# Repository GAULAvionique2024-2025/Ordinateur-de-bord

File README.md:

<h1 align="center">Ordinateur de bord GAUL 2024-2026</h1>

<p align="left">

</p>

## 🌟 **Main Repo pour l'ODB du GAUL**

Ce projet met en œuvre un MCU associé à divers capteurs et modules pour créer un ordinateur de bord performant, optimisé pour un lancement de fusée de type L4. Ce système embarqué est conçu pour collecter et analyser des données en temps réel, permettant ainsi une évaluation précise des performances de la fusée.
De plus, l’ODB est responsable du déclenchement des charges pyrotechniques utilisées pour le déploiement des parachutes et la séparation des étages de la fusée, assurant ainsi la réussite et la sécurité des différentes phases du vol.
L’ensemble forme un système de télémétrie complet, capable non seulement de mesurer et enregistrer les données de vol, mais aussi d’agir activement sur les systèmes de la fusée au bon moment.

> Pour des explications détaillées sur le rôle et le fonctionnement de chaque composant, consultez :
> - [Explications ODB1](./Documentation/ODB1/Explications.md)
> - [Explications ODB2](./Documentation/ODB2/Explications.md)
> - [Explications ODB3 (ODBlix)](./Documentation/ODB2/Explications.md)

## ⚙️ Fonctionnalités de l’Ordinateur de bord (ODB)

Ce document présente une vue d’ensemble des fonctionnalités offertes par l’ordinateur de bord du GAUL.  
Il s’agit d’un résumé fonctionnel, indépendant des détails d’implémentation propres à chaque version.

### 📊 Acquisition et gestion des données
- Mesure des paramètres de vol (accélération, orientation, altitude, température, etc.)
- Acquisition des données à haute fréquence durant les phases critiques du vol
- Synchronisation temporelle des mesures
- Gestion simultanée de plusieurs capteurs
- Support de la redondance des sources de données

### 💾 Enregistrement et stockage
- Enregistrement complet des données de vol pour analyse post-lancement
- Stockage sur mémoire embarquée et/ou carte SD
- Structuration et horodatage des journaux de vol

### 📡 Télémétrie et communication
- Transmission des données de vol en temps réel vers la station au sol
- Communication radio longue portée
- Communication locale pour configuration, tests et débogage
- Support de protocoles de communication adaptés à l’avionique expérimentale

### 🚦 Gestion des événements de vol
- Détection automatique des différentes phases de vol (lancement, apogée, descente, atterrissage)
- Déclenchement conditionnel des événements critiques
- Commande des charges pyrotechniques (déploiement des parachutes, séparation des étages)
- Mécanismes de sécurité contre les déclenchements inattendus

### 🧭 Navigation et localisation
- Intégration des données de positionnement GPS
- Suivi de la trajectoire de vol
- Assistance à la récupération post-vol
- Compatibilité avec notre système de repérage externe ([IdéFIX](https://github.com/GAULAvionique/IdeFIX))

### 🔍 Diagnostic et supervision
- Surveillance de l’état du système en temps réel
- Indication des statuts de fonctionnement et des erreurs
- Outils d’aide au débogage pour les phases de test
- Retour d’information sonore et/ou visuel

### 🧪 Tests et validation
- Support des essais au sol
- Modes de test et de simulation
- Validation progressive avant intégration en vol
- Exploitation des données de vol pour amélioration continue

## 📚 **Documentation**

Toutes les informations sur les composants hardware / logiciel et les drivers sont disponibles ici :

### **Ordinateur de bord 1**
- [Composantes](./Documentation/ODB1/Composantes.md)
- [Drivers](./Documentation/ODB1/Drivers.md)

### **Ordinateur de bord 2**

- [Composantes](./Documentation/ODB2/Composantes.md)
- [Drivers](./Documentation/ODB2/Drivers.md)

### **Ordinateur de bord 3**

- [Composantes](./Documentation/ODB3/Composantes.md)
- [Drivers](./Documentation/ODB3/Drivers.md)

> [Prise en main des logiciels](./Documentation/Logiciel.md)

### 💡 **Liens Utiles**
- Pour voir la première itération de l'ordinateur de bord, consultez le projet [ODB1](https://github.com/GAULAvionique2023-2024/ODB1_Firmware).
- L'environnement de développement intégré pour STM32 est [STM32CubeIDE](https://www.st.com/en/development-tools/stm32cubeide.html). Un document est disponible pour permettre une [prise en main](./Documentation/Logiciel.md) initiale pour le projet.
- [deepbluembedded](https://deepbluembedded.com/stm32-arm-programming-tutorials/) offre des tutoriels sur la programmation STM32.

> Ce projet essaye de suivre les règles de [Conventional Commits](https://www.conventionalcommits.org/en/v1.0.0/) afin de garder un historique clair et cohérent.

## 👥 **Auteurs et Contributeurs**

- [@SamLol12](https://github.com/SamLol12)
- [@bestrider14](https://github.com/bestrider14)
- [@mathouqc](https://github.com/mathouqc)
- [@vides119](https://github.com/vides119)
- [Autres Participants](./Documentation/Participants.md)

---

🏠 Retour à la [page d'accueil](https://github.com/GAULAvionique)

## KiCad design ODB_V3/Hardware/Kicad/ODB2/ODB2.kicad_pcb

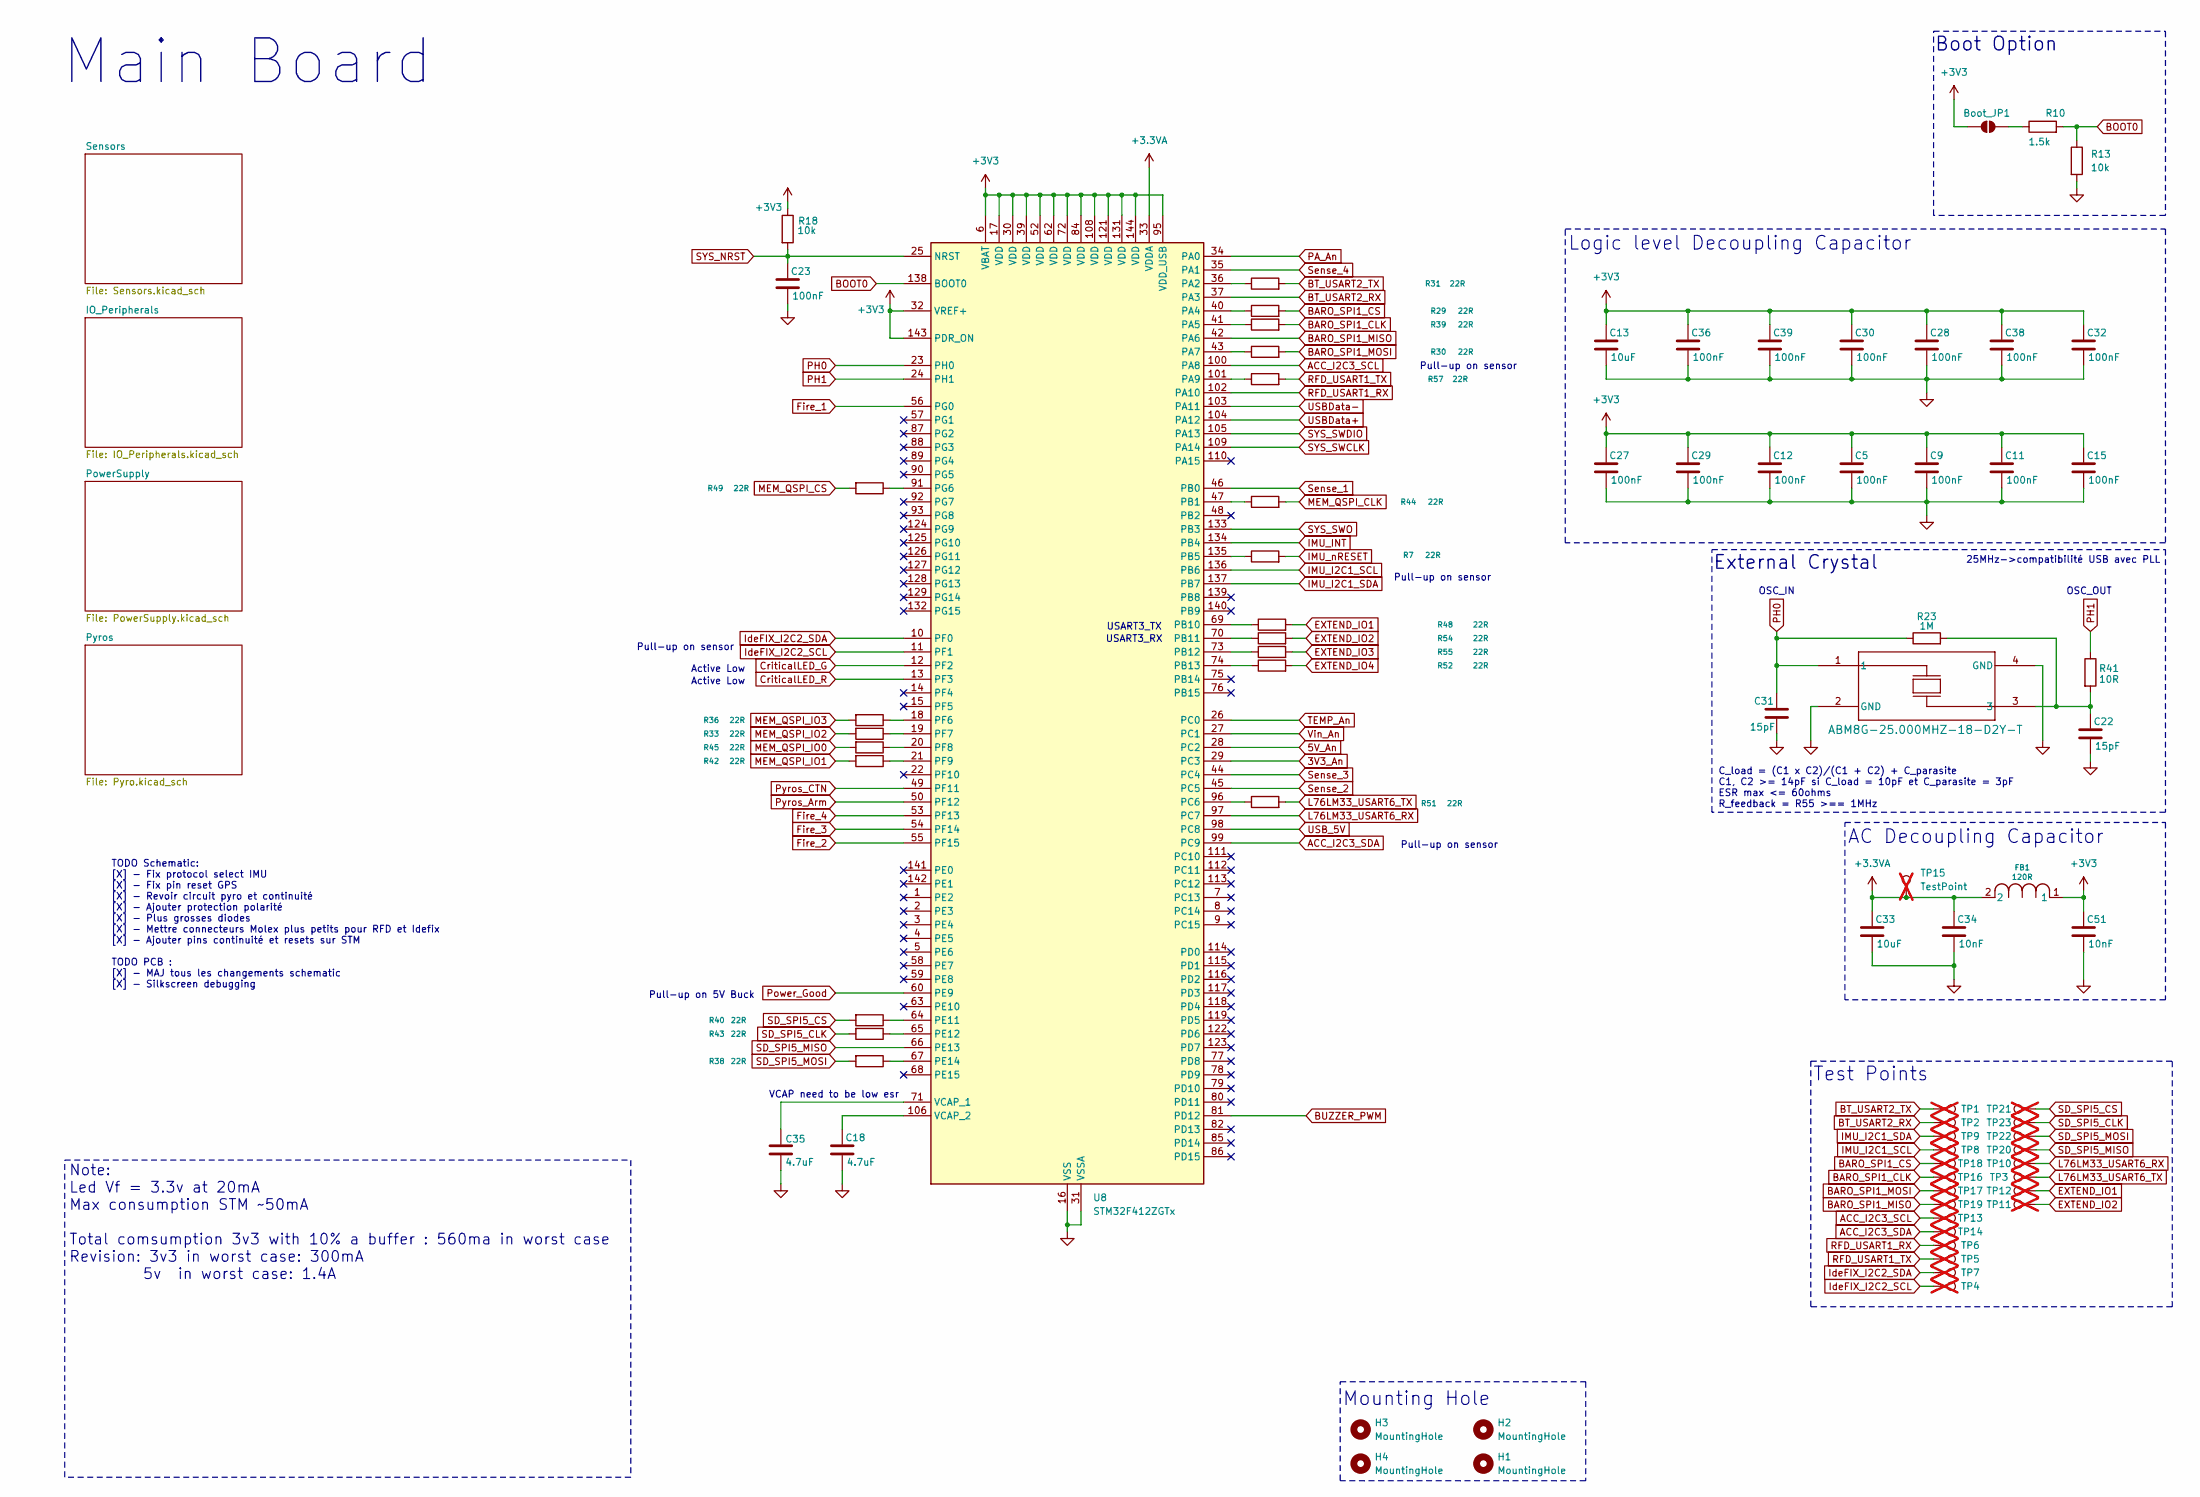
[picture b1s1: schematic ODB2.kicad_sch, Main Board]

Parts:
Boot_JP1: SolderJumper_2_Open; SolderJumper-2_P1.3mm_Open_TrianglePad1.0x1.5mm
C5, C9, C11, C12, C15, C23, C27, C28, C29, C30, C32, C36, C38, C39: 100nF; C_0402_1005Metric; Manufacturer_Part_Number CC0402KRX5R9BB104; DigiKey_Part_Number 311-3342-1-ND
C13, C33: 10uF; C_0603_1608Metric; Manufacturer_Part_Number GMC10X5R106M35NT; DigiKey_Part_Number 4713-GMC10X5R106M35NTTR-ND
C18, C35: 4.7uF; C_0603_1608Metric; Manufacturer_Part_Number NMC0603X5R475K6.3TRPF; DigiKey_Part_Number 4988-NMC0603X5R475K6.3TRPFCT-ND
C22, C31: 15pF; C_0402_1005Metric; Manufacturer_Part_Number GJM1555C1H150FB01D; DigiKey_Part_Number 490-11191-1-ND
C34, C51: 10nF; C_0402_1005Metric; Manufacturer_Part_Number GRM155R71C103KA01D; DigiKey_Part_Number 490-1313-1-ND
FB1: 120R; IND_25_0805_FRT; Manufacturer_Part_Number 2508051217Y6; DigiKey_Part_Number 1934-1472-1-ND
H1, H2, H3, H4: MountingHole; MountingHole_4.3mm_M4
R7, R29, R30, R31, R33, R36, R38, R39, R40, R42, R43, R44, R45, R48, R49, R51, R52, R54, R55, R57: 22R; R_0402_1005Metric; Manufacturer_Part_Number AC0402FR-0722RL; DigiKey_Part_Number YAG3460CT-ND
R10: 1.5k; R_0603_1608Metric; Manufacturer_Part_Number ERA-3AEB152V; DigiKey_Part_Number P1.5KDBCT-ND
R13, R18: 10k; R_0603_1608Metric; Manufacturer_Part_Number RC0603FR-0710KL; DigiKey_Part_Number 311-10.0KHRCT-ND
R23: 1M; R_0402_1005Metric; Manufacturer_Part_Number ERJ-2RKF1004X; DigiKey_Part_Number P1.00MLCT-ND
R41: 10R; R_0402_1005Metric; Manufacturer_Part_Number CRCW040210R0FKED; DigiKey_Part_Number 541-10.0LCT-ND
TP1, TP2, TP3, TP4, TP5, TP6, TP7, TP8, TP9, TP10, TP11, TP12, TP13, TP14, TP15, TP16, TP17, TP18, TP19, TP20, TP21, TP22, TP23: TestPoint; TestPoint_Pad_D1.0mm; not fitted
U8: STM32F412ZGTx; LQFP-144_20x20mm_P0.5mm; Manufacturer_Part_Number STM32F412ZGT6; DigiKey_Part_Number 497-16768-ND
Y1: ABM8G-25.000MHZ-18-D2Y-T; CRYSTAL_ABM8G_ABR; Manufacturer_Part_Number ABM8G-25.000MHZ-18-D2Y-T3; DigiKey_Part_Number 535-14129-1-ND

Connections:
3V3_An: U8.29 (PC3); also elsewhere on the board
3V3_Main: Boot_JP1.1 (A), C5.1, C9.1, C11.1, C12.1, C13.1, C15.1, C27.1, C28.1, C29.1, C30.1, C32.1, C36.1, C38.1, C39.1, C51.1, FB1.1, R18.1, U8.6 (VBAT), U8.17 (VDD), U8.30 (VDD), U8.32 (VREF+), U8.39 (VDD), U8.52 (VDD), U8.62 (VDD), U8.72 (VDD), U8.84 (VDD), U8.95 (VDD_USB), U8.108 (VDD), U8.121 (VDD), U8.131 (VDD), U8.143 (PDR_ON), U8.144 (VDD); also elsewhere on the board
5V_An: U8.28 (PC2); also elsewhere on the board
+3.3VA: C33.1, C34.1, FB1.2, TP15.1, U8.33 (VDDA)
ACC_I2C3_SCL: TP13.1 (1_1), U8.100 (PA8); also elsewhere on the board
ACC_I2C3_SDA: TP14.1 (1_1), U8.99 (PC9); also elsewhere on the board
BARO_SPI1_CLK: R39.2, TP16.1 (1_1); also elsewhere on the board
BARO_SPI1_CS: R29.2, TP18.1 (1_1); also elsewhere on the board
BARO_SPI1_MISO: TP19.1 (1_1), U8.42 (PA6); also elsewhere on the board
BARO_SPI1_MOSI: R30.2, TP17.1 (1_1); also elsewhere on the board
BOOT0: R10.2, R13.1, U8.138 (BOOT0)
BT_USART2_RX: TP2.1 (1_1), U8.37 (PA3); also elsewhere on the board
BT_USART2_TX: R31.2, TP1.1 (1_1); also elsewhere on the board
BUZZER_PWM: U8.81 (PD12); also elsewhere on the board
CriticalLED_G: U8.12 (PF2); also elsewhere on the board
CriticalLED_R: U8.13 (PF3); also elsewhere on the board
EXTEND_IO1: R48.2, TP12.1; also elsewhere on the board
EXTEND_IO2: R54.2, TP11.1; also elsewhere on the board
EXTEND_IO3: R55.2; also elsewhere on the board
EXTEND_IO4: R52.2; also elsewhere on the board
Fire_1: U8.56 (PG0); also elsewhere on the board
Fire_2: U8.55 (PF15); also elsewhere on the board
Fire_3: U8.54 (PF14); also elsewhere on the board
Fire_4: U8.53 (PF13); also elsewhere on the board
GND: C5.2, C9.2, C11.2, C12.2, C13.2, C15.2, C18.2, C22.2, C23.2, C27.2, C28.2, C29.2, C30.2, C31.2, C32.2, C33.2, C34.2, C35.2, C36.2, C38.2, C39.2, C51.2, R13.2, U8.16 (VSS), U8.31 (VSSA), U8.38 (VSS), U8.51 (VSS), U8.61 (VSS), U8.83 (VSS), U8.94 (VSS), U8.107 (VSS), U8.120 (VSS), U8.130 (VSS), Y1.2 (GND), Y1.4 (GND); also elsewhere on the board
IMU_I2C1_SCL: TP8.1 (1_1), U8.136 (PB6); also elsewhere on the board
IMU_I2C1_SDA: TP9.1 (1_1), U8.137 (PB7); also elsewhere on the board
IMU_INT: U8.134 (PB4); also elsewhere on the board
IMU_nRESET: R7.2; also elsewhere on the board
IdeFIX_I2C2_SCL: TP4.1 (1_1), U8.11 (PF1); also elsewhere on the board
IdeFIX_I2C2_SDA: TP7.1 (1_1), U8.10 (PF0); also elsewhere on the board
L76LM33_USART6_RX: TP10.1 (1_1), U8.97 (PC7); also elsewhere on the board
L76LM33_USART6_TX: R51.2, TP3.1 (1_1); also elsewhere on the board
MEM_QSPI_CLK: R44.2; also elsewhere on the board
MEM_QSPI_CS: R49.2; also elsewhere on the board
MEM_QSPI_IO0: R45.2; also elsewhere on the board
MEM_QSPI_IO1: R42.2; also elsewhere on the board
MEM_QSPI_IO2: R33.2; also elsewhere on the board
MEM_QSPI_IO3: R36.2; also elsewhere on the board
unnamed: Boot_JP1.2 (B), R10.1
unnamed: C22.1, R23.2, R41.2, Y1.3
unnamed: R31.1, U8.36 (PA2)
unnamed: R29.1, U8.40 (PA4)
unnamed: R39.1, U8.41 (PA5)
unnamed: R30.1, U8.43 (PA7)
unnamed: R57.1, U8.101 (PA9)
unnamed: R44.1, U8.47 (PB1)
unnamed: R7.1, U8.135 (PB5)
unnamed: R48.1, U8.69 (PB10)
unnamed: R54.1, U8.70 (PB11)
unnamed: R55.1, U8.73 (PB12)
unnamed: R52.1, U8.74 (PB13)
unnamed: R51.1, U8.96 (PC6)
unnamed: R40.1, U8.64 (PE11)
unnamed: R43.1, U8.65 (PE12)
unnamed: R38.1, U8.67 (PE14)
unnamed: R36.1, U8.18 (PF6)
unnamed: R33.1, U8.19 (PF7)
unnamed: R45.1, U8.20 (PF8)
unnamed: R42.1, U8.21 (PF9)
unnamed: R49.1, U8.91 (PG6)
unnamed: C35.1, U8.71 (VCAP_1)
unnamed: C18.1, U8.106 (VCAP_2)
PA_An: U8.34 (PA0); also elsewhere on the board
PH0: C31.1, R23.1, U8.23 (PH0), Y1.1
PH1: R41.1, U8.24 (PH1)
Power_Good: U8.60 (PE9); also elsewhere on the board
Pyros_Arm: U8.50 (PF12); also elsewhere on the board
Pyros_CTN: U8.49 (PF11); also elsewhere on the board
RFD_USART1_RX: TP6.1 (1_1), U8.102 (PA10); also elsewhere on the board
RFD_USART1_TX: R57.2, TP5.1 (1_1); also elsewhere on the board
SD_SPI5_CLK: R43.2, TP23.1 (1_1); also elsewhere on the board
SD_SPI5_CS: R40.2, TP21.1 (1_1); also elsewhere on the board
SD_SPI5_MISO: TP20.1 (1_1), U8.66 (PE13); also elsewhere on the board
SD_SPI5_MOSI: R38.2, TP22.1 (1_1); also elsewhere on the board
SYS_NRST: C23.1, R18.2, U8.25 (NRST); also elsewhere on the board
SYS_SWCLK: U8.109 (PA14); also elsewhere on the board
SYS_SWDIO: U8.105 (PA13); also elsewhere on the board
SYS_SWO: U8.133 (PB3); also elsewhere on the board
Sense_1: U8.46 (PB0); also elsewhere on the board
Sense_2: U8.45 (PC5); also elsewhere on the board
Sense_3: U8.44 (PC4); also elsewhere on the board
Sense_4: U8.35 (PA1); also elsewhere on the board
TEMP_An: U8.26 (PC0); also elsewhere on the board
USBData+: U8.104 (PA12); also elsewhere on the board
USBData-: U8.103 (PA11); also elsewhere on the board
USB_5V: U8.98 (PC8); also elsewhere on the board
Vin_An: U8.27 (PC1); also elsewhere on the board

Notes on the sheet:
VCAP need to be low esr
Pull-up on sensor
25MHz->compatibilité USB avec PLL
C_load = (C1 x C2)/(C1 + C2) + C_parasite C1, C2 >= 14pF si C_load = 10pF et C_parasite = 3pF ESR max <= 60ohms R_feedback = R55 >== 1MHz
Active Low
Pull-up on 5V Buck
Main Board
Mounting Hole
Boot Option
USART3_TX
Note: Led Vf = 3.3v at 20mA Max consumption STM ~50mA Total comsumption 3v3 with 10% a buffer : 560ma in worst case Revision: 3v3 in worst case: 300mA 5v in worst case: 1.4A
AC Decoupling Capacitor
OSC_OUT
Test Points
External Crystal
Logic level Decoupling Capacitor
OSC_IN
TODO Schematic: [X] - Fix protocol select IMU [X] - Fix pin reset GPS [X] - Revoir circuit pyro et continuité [X] - Ajouter protection polarité [X] - Plus grosses diodes [X] - Mettre connecteurs Molex plus petits pour RFD et Idefix [X] - Ajouter pins continuité et resets sur STM TODO PCB : [X] - MA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
USART3_RX

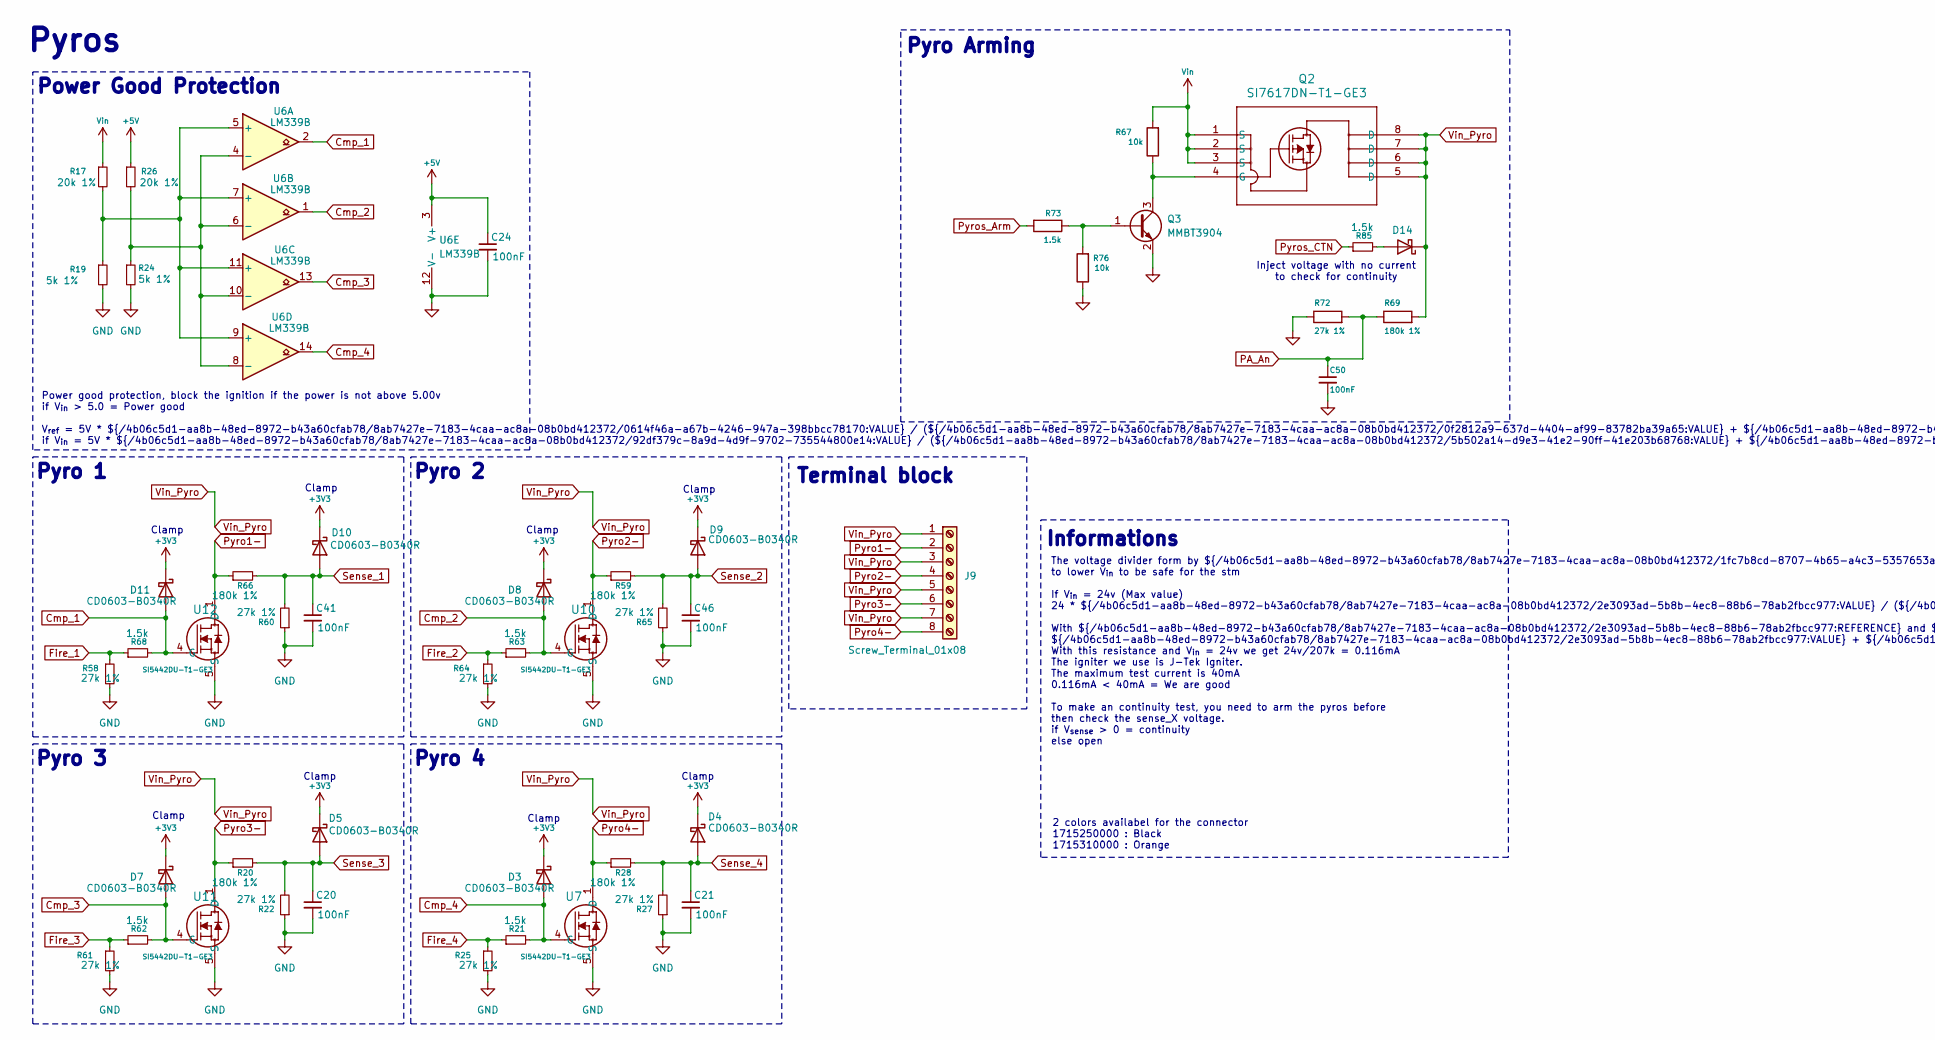
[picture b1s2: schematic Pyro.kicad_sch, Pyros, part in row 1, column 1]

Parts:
C20, C21, C24, C41, C46, C50: 100nF; C_0402_1005Metric; Manufacturer_Part_Number CC0402KRX5R9BB104; DigiKey_Part_Number 311-3342-1-ND
D3, D4, D5, D7, D8, D9, D10, D11, D14: CD0603-B0340R; D_0603_1608Metric; Manufacturer_Part_Number CD0603-B0340R; DigiKey_Part_Number CD0603-B0340RCT-ND
J9: Screw_Terminal_01x08; 8pin_terminal_2mm54; Manufacturer_Part_Number 1725711; DigiKey_Part_Number 277-1279-ND
Q2: SI7617DN-T1-GE3; POWERPAK_1212-8_VIS; Manufacturer_Part_Number SI7617DN-T1-GE3; DigiKey_Part_Number SI7617DN-T1-GE3CT-ND
Q3: MMBT3904; SOT-23; Manufacturer_Part_Number MMBT3904LT1G; DigiKey_Part_Number MMBT3904LT1GOSCT-ND
R17, R26: 20k 1%; R_0603_1608Metric; Manufacturer_Part_Number ERA-3AEB203V; DigiKey_Part_Number P20KDBCT-ND
R19, R24: 5k 1%; R_0603_1608Metric; Manufacturer_Part_Number MCT06030D5001BP500; DigiKey_Part_Number 541-MCT06030D5001BP500CT-ND
R20, R28, R59, R66, R69: 180k 1%; R_0603_1608Metric; Manufacturer_Part_Number ERA-3AEB184V; DigiKey_Part_Number P180KDBCT-ND
R21, R62, R63, R68, R73, R85: 1.5k; R_0603_1608Metric; Manufacturer_Part_Number ERA-3AEB152V; DigiKey_Part_Number P1.5KDBCT-ND
R22, R25, R27, R58, R60, R61, R64, R65, R72: 27k 1%; R_0603_1608Metric; Manufacturer_Part_Number RG1608P-273-B-T5; DigiKey_Part_Number RG16P27.0KBCT-ND
R67, R76: 10k; R_0603_1608Metric; Manufacturer_Part_Number RC0603FR-0710KL; DigiKey_Part_Number 311-10.0KHRCT-ND
U6: LM339B; TSSOP-14_4.4x5mm_P0.65mm; Manufacturer_Part_Number LM339BIPWR; DigiKey_Part_Number 296-LM339BIPWRCT-ND
U7, U10, U11, U12: SI5442DU-T1-GE3; SON_8DU-T1-GE3_VIS; Manufacturer_Part_Number SI5442DU-T1-GE3; DigiKey_Part_Number SI5442DU-T1-GE3CT-ND

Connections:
3V3_Main: D3.1 (K), D4.1 (K), D5.1 (K), D7.1 (K), D8.1 (K), D9.1 (K), D10.1 (K), D11.1 (K); also elsewhere on the board
5V_Main: C24.1, R26.1, U6.3 (V+); also elsewhere on the board
Cmp_1: D11.2 (A), R68.2, U6.2, U12.4 (G)
Cmp_2: D8.2 (A), R63.2, U6.1, U10.4 (G)
Cmp_3: D7.2 (A), R62.2, U6.13, U11.4 (G)
Cmp_4: D3.2 (A), R21.2, U6.14, U7.4 (G)
Fire_1: R58.1, R68.1; also elsewhere on the board
Fire_2: R63.1, R64.1; also elsewhere on the board
Fire_3: R61.1, R62.1; also elsewhere on the board
Fire_4: R21.1, R25.1; also elsewhere on the board
GND: C20.2, C21.2, C24.2, C41.2, C46.2, C50.2, Q3.2 (E), R19.2, R22.1, R24.2, R25.2, R27.1, R58.2, R60.1, R61.2, R64.2, R65.1, R72.1, R76.1, U6.12 (V-), U7.5 (S), U7.9 (S), U10.5 (S), U10.9 (S), U11.5 (S), U11.9 (S), U12.5 (S), U12.9 (S); also elsewhere on the board
unnamed: D14.2 (A), R85.2
unnamed: Q2.4 (G), Q3.3 (C), R67.1
unnamed: Q3.1 (B), R73.1, R76.2
unnamed: R17.2, R19.1, U6.5 (+), U6.7 (+), U6.9 (+), U6.11 (+)
unnamed: R24.1, R26.2, U6.4 (-), U6.6 (-), U6.8 (-), U6.10 (-)
PA_An: C50.1, R69.1, R72.2; also elsewhere on the board
Pyro1-: J9.2, R66.1, U12.1 (D), U12.2 (D), U12.3 (D), U12.6 (D), U12.7 (D), U12.8 (D), U12.10 (D)
Pyro2-: J9.4, R59.1, U10.1 (D), U10.2 (D), U10.3 (D), U10.6 (D), U10.7 (D), U10.8 (D), U10.10 (D)
Pyro3-: J9.6, R20.1, U11.1 (D), U11.2 (D), U11.3 (D), U11.6 (D), U11.7 (D), U11.8 (D), U11.10 (D)
Pyro4-: J9.8, R28.1, U7.1 (D), U7.2 (D), U7.3 (D), U7.6 (D), U7.7 (D), U7.8 (D), U7.10 (D)
Pyros_Arm: R73.2; also elsewhere on the board
Pyros_CTN: R85.1; also elsewhere on the board
Sense_1: C41.1, D10.2 (A), R60.2, R66.2; also elsewhere on the board
Sense_2: C46.1, D9.2 (A), R59.2, R65.2; also elsewhere on the board
Sense_3: C20.1, D5.2 (A), R20.2, R22.2; also elsewhere on the board
Sense_4: C21.1, D4.2 (A), R27.2, R28.2; also elsewhere on the board
VIN_Filtered: Q2.1 (S), Q2.2 (S), Q2.3 (S), R17.1, R67.2; also elsewhere on the board
Vin_Pyro: D14.1 (K), J9.1, J9.3, J9.5, J9.7, Q2.5 (D), Q2.6 (D), Q2.7 (D), Q2.8 (D), Q2.9 (D), R69.2

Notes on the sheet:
Pyro Arming
Clamp
Pyro 1
Pyros
Power good protection, block the ignition if the power is not above 5.00v if V_{in} > 5.0 = Power good V_{ref} = 5V * ${/4b06c5d1-aa8b-48ed-8972-b43a60cfab78/8ab7427e-7183-4caa-ac8a-08b0bd412372/0614f46a-a67b-4246-947a-398bbcc78170:VALUE} / (${/4b06c5d1-aa8b-48ed-8972-b43a60cfab78/8ab7427e-7183-4ca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
Pyro 4
Pyro 2
2 colors availabel for the connector 1715250000 : Black 1715310000 : Orange
The voltage divider form by ${/4b06c5d1-aa8b-48ed-8972-b43a60cfab78/8ab7427e-7183-4caa-ac8a-08b0bd412372/1fc7b8cd-8707-4b65-a4c3-5357653aeaad:REFERENCE} and ${/4b06c5d1-aa8b-48ed-8972-b43a60cfab78/8ab7427e-7183-4caa-ac8a-08b0bd412372/2e3093ad-5b8b-4ec8-88b6-78ab2fbcc977:REFERENCE} are there to lowe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
Power Good Protection
Inject voltage with no current to check for continuity
Terminal block
Informations
Pyro 3

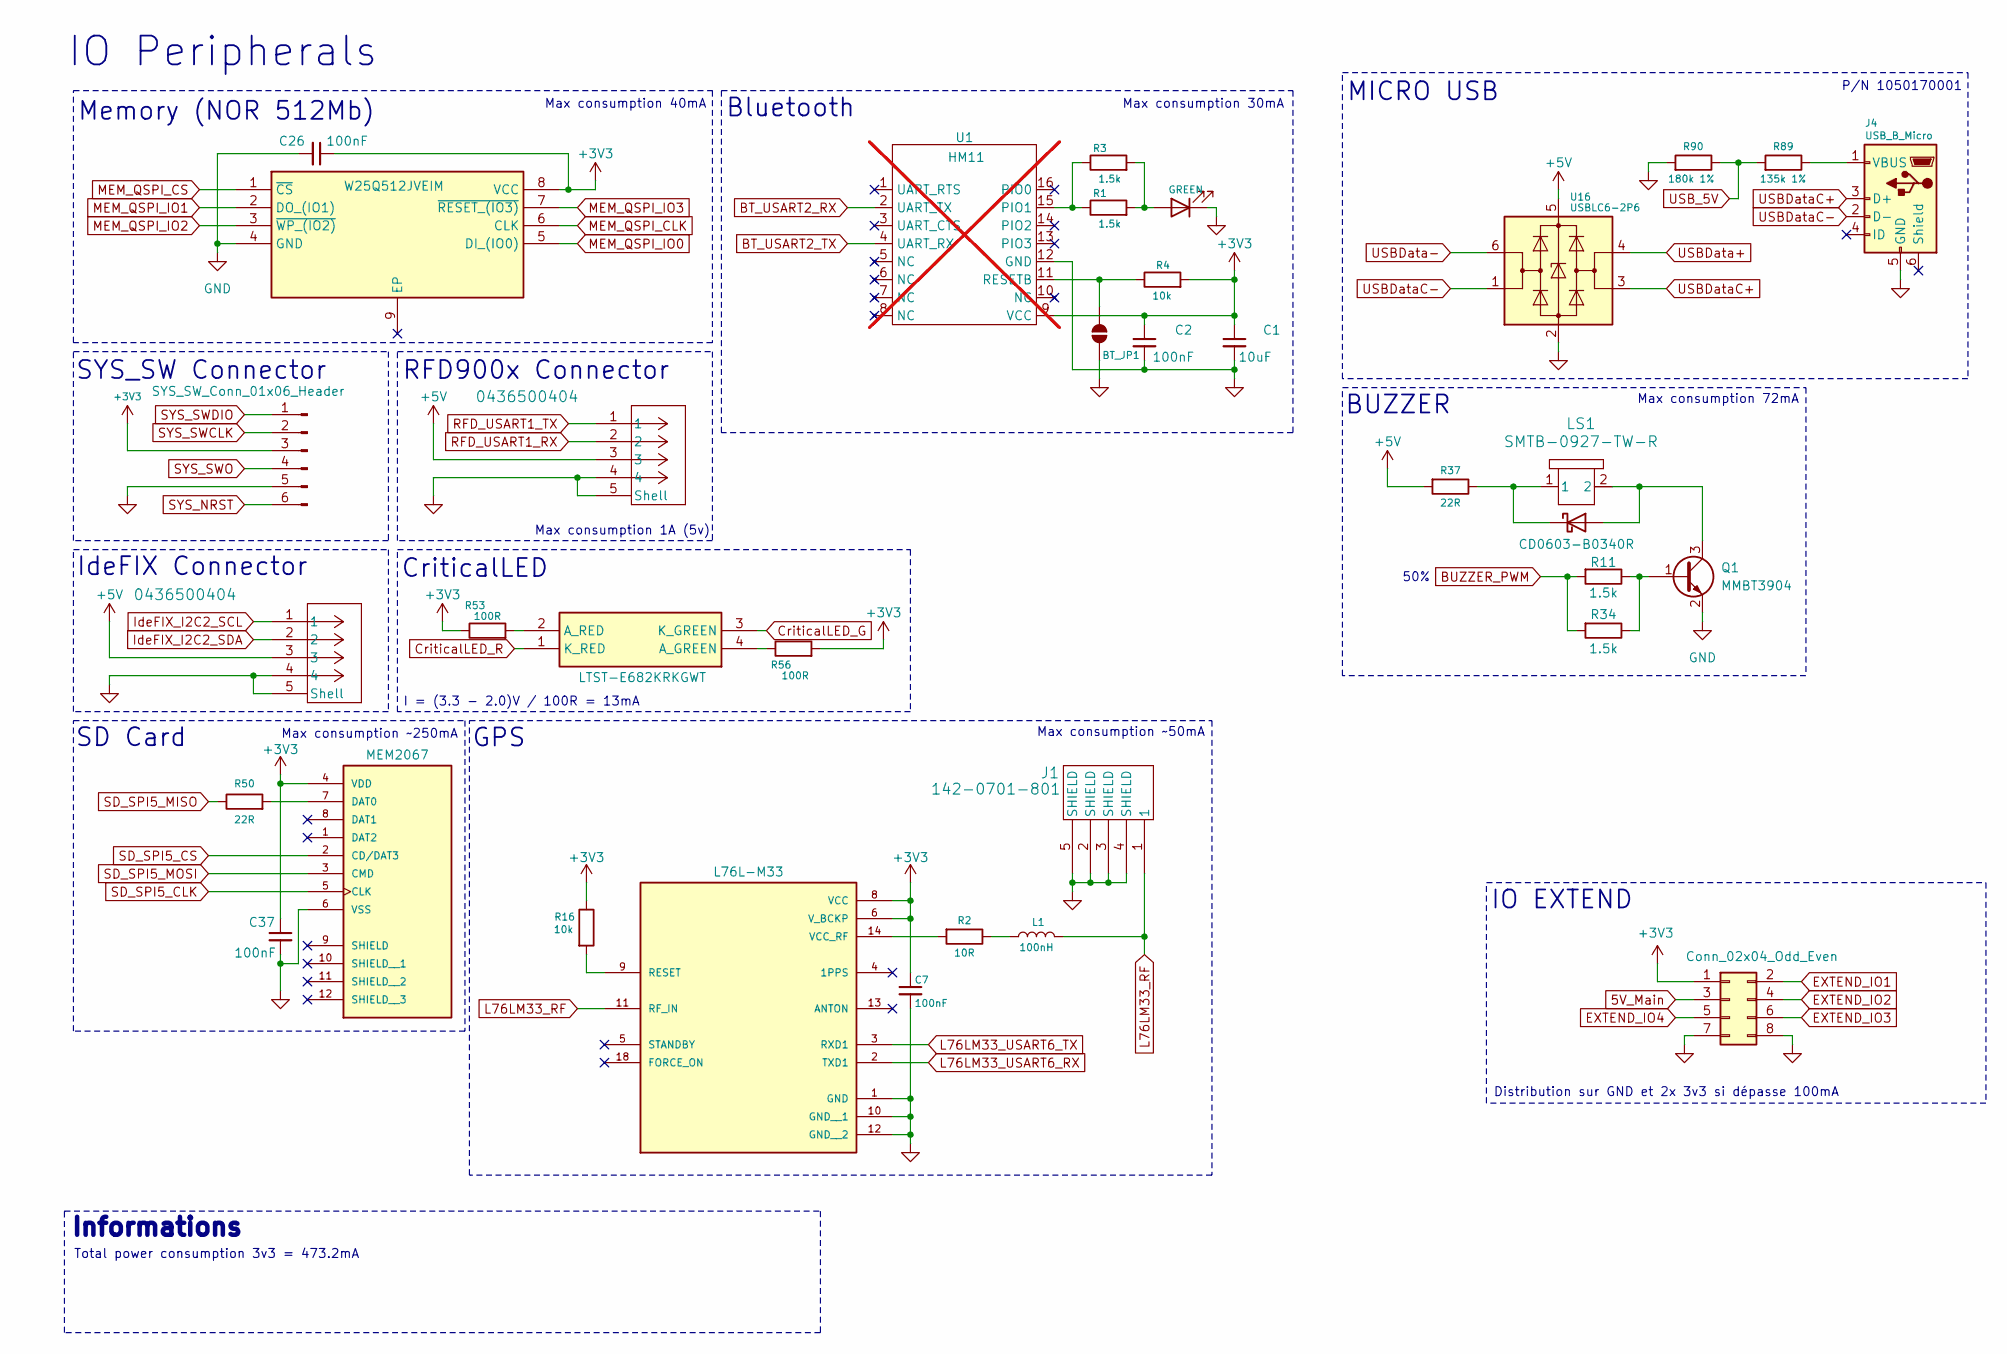
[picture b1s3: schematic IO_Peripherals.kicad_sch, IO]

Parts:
BT_JP1: SolderJumper_2_Open; SolderJumper-2_P1.3mm_Open_TrianglePad1.0x1.5mm
C1: 10uF; C_0603_1608Metric; Manufacturer_Part_Number GMC10X5R106M35NT; DigiKey_Part_Number 4713-GMC10X5R106M35NTTR-ND
C2, C7, C26, C37: 100nF; C_0402_1005Metric; Manufacturer_Part_Number CC0402KRX5R9BB104; DigiKey_Part_Number 311-3342-1-ND
D1: GREEN; LED_QBLP601-AG15; Manufacturer_Part_Number QBLP601-AG15; DigiKey_Part_Number 1516-QBLP601-AG15CT-ND
D2: CD0603-B0340R; D_0603_1608Metric; Manufacturer_Part_Number CD0603-B0340R; DigiKey_Part_Number CD0603-B0340RCT-ND
D6: LTST-E682KRKGWT; LTSTE683RGBW; Mouser Part Number 859-LTST-E682KRKGWT
J1: 142-0701-801; CONN_142-0701-801; Manufacturer_Part_Number 142-0701-801; DigiKey_Part_Number J502-ND
J2, J3: 0436500404; CONN_SD-43650-002_04_MOL; Manufacturer_Part_Number 0436500404; DigiKey_Part_Number WM1877-ND
J4: USB_B_Micro; USB_Micro-B_Molex-105017-0001; Manufacturer_Part_Number 1050170001; DigiKey_Part_Number WM1399CT-ND
J5: SYS_SW_Conn_01x06_Header; PinHeader_1x06_P2.54mm_Vertical; Manufacturer_Part_Number 61300611121; DigiKey_Part_Number 732-5319-ND
J7: Conn_02x04_Odd_Even; PinHeader_2x04_P2.54mm_Vertical; Manufacturer_Part_Number 61300821121; DigiKey_Part_Number 732-5296-ND
J10: MEM2067; GCT_MEM2067-02-180-00-A_REVB; Manufacturer_Part_Number MEM2067-02-180-00-A; DigiKey_Part_Number 2073-MEM2067-02-180-00-ACT-ND
L1: 100nH; L_0603_1608Metric; Manufacturer_Part_Number AIML-0603-R10K-T; DigiKey_Part_Number 535-11609-1-ND
LS1: SMTB-0927-TW-R; SMTB-0927-TW-R_PUI; Manufacturer_Part_Number SMTB-0927-TW-R; DigiKey_Part_Number 668-SMTB-0927-TW-RCT-ND
Q1: MMBT3904; SOT-23; Manufacturer_Part_Number MMBT3904LT1G; DigiKey_Part_Number MMBT3904LT1GOSCT-ND
R1, R3, R11, R34: 1.5k; R_0603_1608Metric; Manufacturer_Part_Number ERA-3AEB152V; DigiKey_Part_Number P1.5KDBCT-ND
R2: 10R; R_0402_1005Metric; Manufacturer_Part_Number CRCW040210R0FKED; DigiKey_Part_Number 541-10.0LCT-ND
R4, R16: 10k; R_0603_1608Metric; Manufacturer_Part_Number RC0603FR-0710KL; DigiKey_Part_Number 311-10.0KHRCT-ND
R37: 22R; R_0402_1005Metric; Manufacturer_Part_Number 2019-SG73P1EWTTP22R0FTR-ND; DigiKey_Part_Number SG73P1EWTTP22R0F
R50: 22R; R_0402_1005Metric; Manufacturer_Part_Number AC0402FR-0722RL; DigiKey_Part_Number YAG3460CT-ND
R53, R56: 100R; R_0603_1608Metric; Manufacturer_Part_Number PCAN0603E1000BST5; DigiKey_Part_Number 764-1252-1-ND
R89: 135k 1%; R_0603_1608Metric; Manufacturer_Part_Number RT0603BRD07135KL; DigiKey_Part_Number 13-RT0603BRD07135KLCT-ND
R90: 180k 1%; R_0603_1608Metric; Manufacturer_Part_Number ERA-3AEB184V; DigiKey_Part_Number P180KDBCT-ND
U1: HM11; hm11; not fitted
U2: L76L-M33; Quectel_L76; Manufacturer_Part_Number L76L-M33; DigiKey_Part_Number 2958-L76L-M33CT-ND
U9: W25Q512JVEIM; SON127P800X600X80-9N-D; Mouser Part Number 454-W25Q512JVEIQ
U16: USBLC6-2P6; SOT-666; Manufacturer_Part_Number USBLC6-2P6; DigiKey_Part_Number 497-5026-1-ND

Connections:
3V3_Main: C1.1, C2.1, C7.1, C26.1, C37.1, J5.3, J7.1, J10.4 (VDD), R4.2, R16.1, R53.1, R56.2, U1.9 (VCC), U2.6 (V_BCKP), U2.8 (VCC), U9.8 (VCC); also elsewhere on the board
5V_Main: J2.3, J3.3, J7.3, R37.2, U16.5 (VBUS); also elsewhere on the board
BT_USART2_RX: U1.2 (UART_TX); also elsewhere on the board
BT_USART2_TX: U1.4 (UART_RX); also elsewhere on the board
BUZZER_PWM: R11.2, R34.2; also elsewhere on the board
CriticalLED_G: D6.3 (K_GREEN); also elsewhere on the board
CriticalLED_R: D6.1 (K_RED); also elsewhere on the board
EXTEND_IO1: J7.2; also elsewhere on the board
EXTEND_IO2: J7.4; also elsewhere on the board
EXTEND_IO3: J7.6; also elsewhere on the board
EXTEND_IO4: J7.5; also elsewhere on the board
GND: BT_JP1.1 (A), C1.2, C2.2, C7.2, C26.2, C37.2, D1.1 (K), J1.2 (SHIELD), J1.3 (SHIELD), J1.4 (SHIELD), J1.5 (SHIELD), J2.4, J2.5 (Shell), J2.6 (Shell), J2.7 (Shell), J2.8 (Shell), J3.4, J3.5 (Shell), J3.6 (Shell), J3.7 (Shell), J3.8 (Shell), J4.5 (GND), J5.5, J7.7, J7.8, J10.6 (VSS), Q1.2 (E), R90.2, U1.12 (GND), U2.1 (GND), U2.10 (GND__1), U2.12 (GND__2), U9.4 (GND), U16.2 (GND); also elsewhere on the board
IdeFIX_I2C2_SCL: J2.1; also elsewhere on the board
IdeFIX_I2C2_SDA: J2.2; also elsewhere on the board
L76LM33_RF: J1.1, L1.2, U2.11 (RF_IN)
L76LM33_USART6_RX: U2.2 (TXD1); also elsewhere on the board
L76LM33_USART6_TX: U2.3 (RXD1); also elsewhere on the board
MEM_QSPI_CLK: U9.6 (CLK); also elsewhere on the board
MEM_QSPI_CS: U9.1 (~CS); also elsewhere on the board
MEM_QSPI_IO0: U9.5 (DI_(IO0)); also elsewhere on the board
MEM_QSPI_IO1: U9.2 (DO_(IO1)); also elsewhere on the board
MEM_QSPI_IO2: U9.3 (~WP_(IO2)); also elsewhere on the board
MEM_QSPI_IO3: U9.7 (~RESET_(IO3)); also elsewhere on the board
unnamed: BT_JP1.2 (B), R4.1, U1.11 (RESETB)
unnamed: D1.2 (A), R1.2, R3.2
unnamed: D2.2 (A), LS1.2, Q1.3 (C)
unnamed: D2.1 (K), LS1.1, R37.1
unnamed: D6.4 (A_GREEN), R56.1
unnamed: D6.2 (A_RED), R53.2
unnamed: J4.1 (VBUS), R89.1
unnamed: J10.7 (DAT0), R50.2
unnamed: L1.1, R2.1
unnamed: Q1.1 (B), R11.1, R34.1
unnamed: R1.1, R3.1, U1.15 (PIO1)
unnamed: R16.2, U2.9 (RESET)
unnamed: R2.2, U2.14 (VCC_RF)
RFD_USART1_RX: J3.2; also elsewhere on the board
RFD_USART1_TX: J3.1; also elsewhere on the board
SD_SPI5_CLK: J10.5 (CLK); also elsewhere on the board
SD_SPI5_CS: J10.2 (CD/DAT3); also elsewhere on the board
SD_SPI5_MISO: R50.1; also elsewhere on the board
SD_SPI5_MOSI: J10.3 (CMD); also elsewhere on the board
SYS_NRST: J5.6; also elsewhere on the board
SYS_SWCLK: J5.2; also elsewhere on the board
SYS_SWDIO: J5.1; also elsewhere on the board
SYS_SWO: J5.4; also elsewhere on the board
USBData+: U16.4 (I/O2); also elsewhere on the board
USBData-: U16.6 (I/O1); also elsewhere on the board
USBDataC+: J4.3 (D+), U16.3 (I/O2)
USBDataC-: J4.2 (D-), U16.1 (I/O1)
USB_5V: R89.2, R90.1; also elsewhere on the board

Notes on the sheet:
IO EXTEND
Max consumption 72mA
Max consumption ~250mA
IO Peripherals
Bluetooth
GPS
SD Card
Memory (NOR 512Mb)
Total power consumption 3v3 = 473.2mA
50%
IdeFIX Connector
Max consumption 40mA
Max consumption ~50mA
Informations
Max consumption 1A (5v)
CriticalLED
MICRO USB
P/N 1050170001
I = (3.3 - 2.0)V / 100R = 13mA
BUZZER
Max consumption 30mA
Distribution sur GND et 2x 3v3 si dépasse 100mA
RFD900x Connector
SYS_SW Connector
